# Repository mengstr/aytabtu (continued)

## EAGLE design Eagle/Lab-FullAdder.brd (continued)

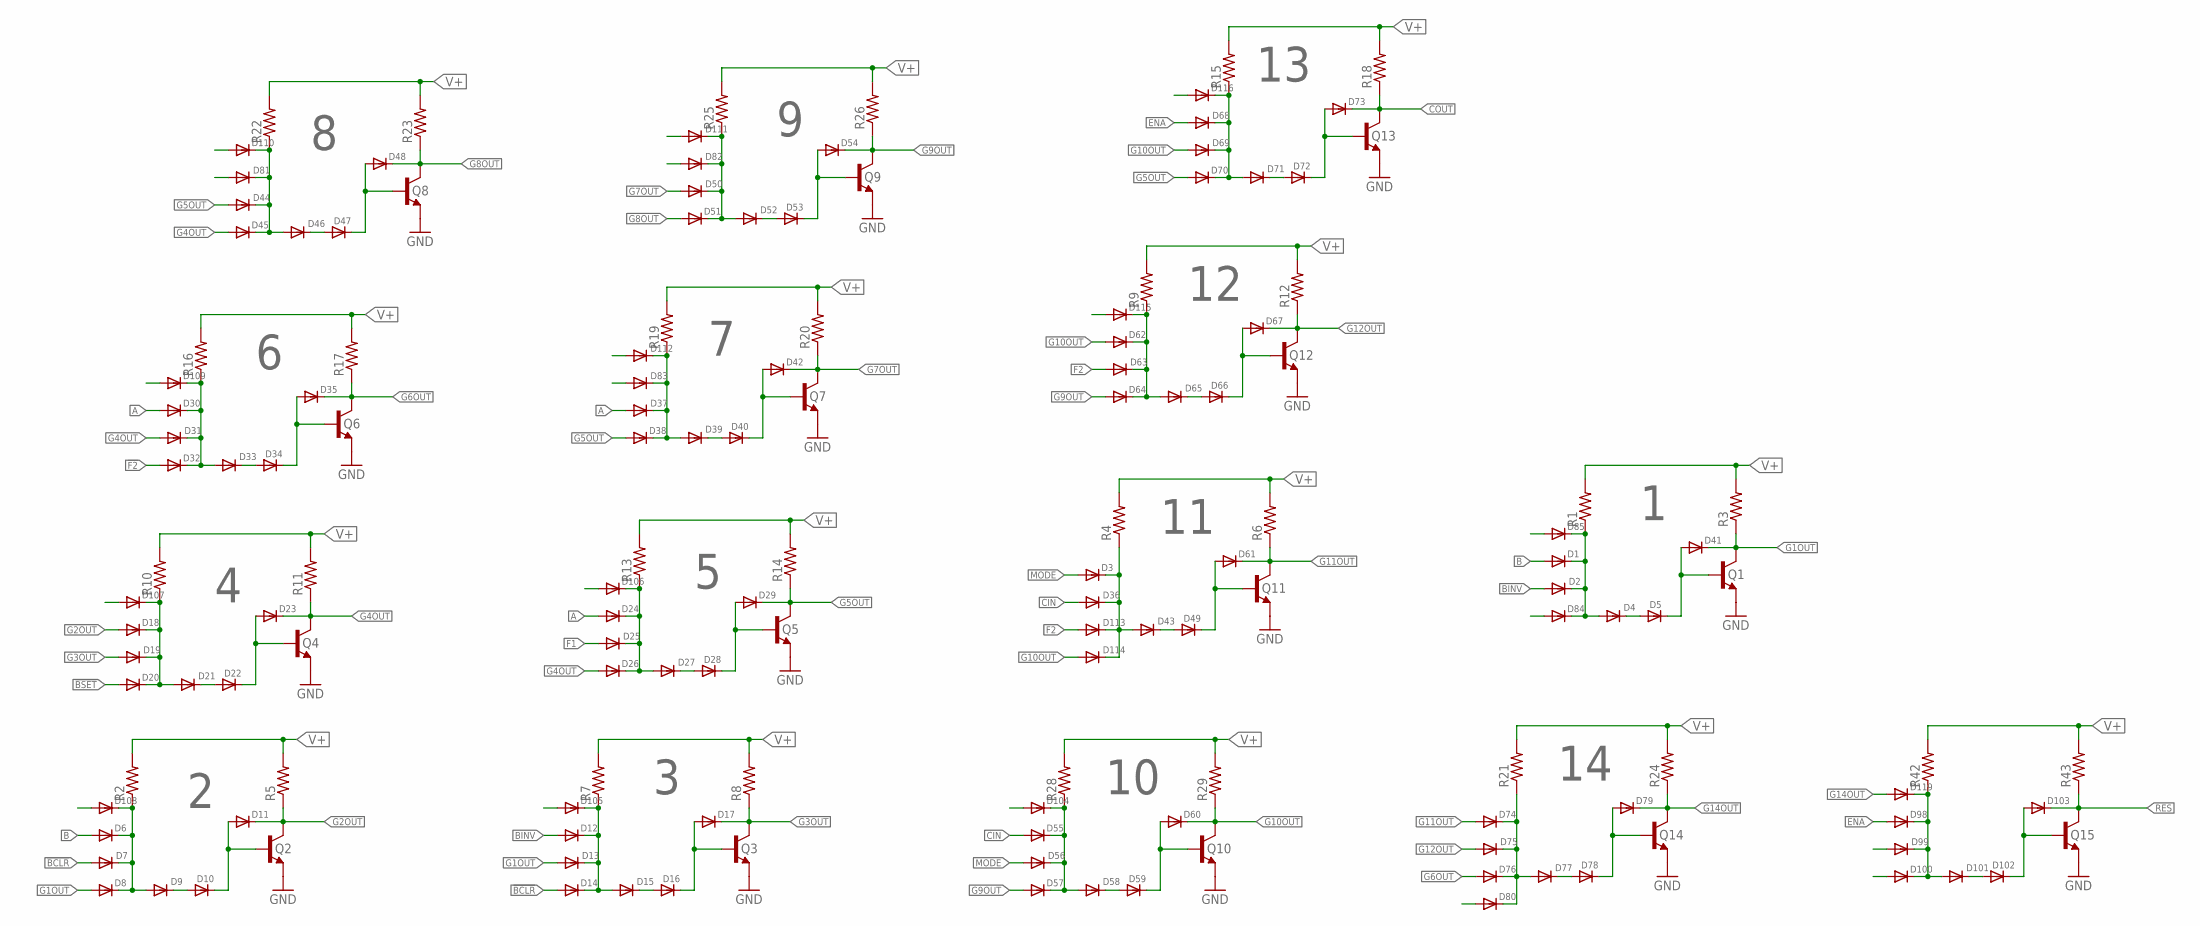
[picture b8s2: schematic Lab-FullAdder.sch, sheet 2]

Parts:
D1, D2, D3, D4, D5, D6, D7, D8, D9, D10, D12, D13, D14, D15, D16, D18, D19, D20, D21, D22, D24, D25, D26, D27, D28, D30, D31, D32, D33, D34, D36, D37, D38, D39, D40, D43, D44, D45, D46, D47, D49, D50, D51, D52, D53, D55, D56, D57, D58, D59, D62, D63, D64, D65, D66, D68, D69, D70, D71, D72, D74, D75, D76, D77, D78, D80, D81, D82, D83, D84, D85, D98, D99, D100, D101, D102, D104, D105, D106, D107, D108, D109, D110, D111, D112, D113, D114, D115, D116, D119: DIODE-6.3; DO35-6.3
D11, D17, D23, D29, D35, D41, D42, D48, D54, D60, D61, D67, D73, D79, D103: DIODE-7.6; DO35-7.6
Q1, Q2, Q3, Q4, Q5, Q6, Q7, Q8, Q9, Q10, Q11, Q12, Q13, Q14, Q15: 2N3904-1; TO92BH
R1, R2, R3, R4, R5, R6, R7, R8, R9, R10, R11, R12, R13, R14, R15, R16, R17, R18, R19, R20, R21, R22, R23, R24, R25, R26, R28, R29, R42, R43: R1/8-7.6MM; R0125-7.6

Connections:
!BCLR: D7.A, D14.A; also elsewhere on the board
!BSET: D20.A; also elsewhere on the board
!F2: D32.A; also elsewhere on the board
A: D24.A, D30.A, D37.A; also elsewhere on the board
B: D1.A, D6.A; also elsewhere on the board
BINV: D2.A, D12.A; also elsewhere on the board
CIN: D36.A, D55.A; also elsewhere on the board
COUT: D73.C, Q13.3 (C), R18.1; also elsewhere on the board
ENA: D68.A, D98.A; also elsewhere on the board
F1: D25.A; also elsewhere on the board
F2: D63.A, D113.A; also elsewhere on the board
G1OUT: D8.A, D13.A, D41.C, Q1.3 (C), R3.1
G2OUT: D11.C, D18.A, Q2.3 (C), R5.1
G3OUT: D17.C, D19.A, Q3.3 (C), R8.1
G4OUT: D23.C, D26.A, D31.A, D45.A, Q4.3 (C), R11.1
G5OUT: D29.C, D38.A, D44.A, D70.A, Q5.3 (C), R14.1
G6OUT: D35.C, D76.A, Q6.3 (C), R17.1
G7OUT: D42.C, D50.A, Q7.3 (C), R20.1
G8OUT: D48.C, D51.A, Q8.3 (C), R23.1
G9OUT: D54.C, D57.A, D64.A, Q9.3 (C), R26.1
G10OUT: D60.C, D62.A, D69.A, D114.A, Q10.3 (C), R29.1
G11OUT: D61.C, D74.A, Q11.3 (C), R6.1
G12OUT: D67.C, D75.A, Q12.3 (C), R12.1
G14OUT: D79.C, D119.A, Q14.3 (C), R24.1
GND: Q1.1 (E), Q2.1 (E), Q3.1 (E), Q4.1 (E), Q5.1 (E), Q6.1 (E), Q7.1 (E), Q8.1 (E), Q9.1 (E), Q10.1 (E), Q11.1 (E), Q12.1 (E), Q13.1 (E), Q14.1 (E), Q15.1 (E); also elsewhere on the board
MODE: D3.A, D56.A; also elsewhere on the board
unnamed: D1.C, D2.C, D4.A, D84.C, D85.C, R1.1
unnamed: D4.C, D5.A
unnamed: D5.C, D41.A, Q1.2 (B)
unnamed: D6.C, D7.C, D8.C, D9.A, D108.C, R2.1
unnamed: D9.C, D10.A
unnamed: D10.C, D11.A, Q2.2 (B)
unnamed: D3.C, D36.C, D43.A, D113.C, D114.C, R4.1
unnamed: D12.C, D13.C, D14.C, D15.A, D105.C, R7.1
unnamed: D15.C, D16.A
unnamed: D16.C, D17.A, Q3.2 (B)
unnamed: D43.C, D49.A
unnamed: D18.C, D19.C, D20.C, D21.A, D107.C, R10.1
unnamed: D21.C, D22.A
unnamed: D22.C, D23.A, Q4.2 (B)
unnamed: D49.C, D61.A, Q11.2 (B)
unnamed: D24.C, D25.C, D26.C, D27.A, D106.C, R13.1
unnamed: D27.C, D28.A
unnamed: D28.C, D29.A, Q5.2 (B)
unnamed: D30.C, D31.C, D32.C, D33.A, D109.C, R16.1
unnamed: D33.C, D34.A
unnamed: D34.C, D35.A, Q6.2 (B)
unnamed: D98.C, D99.C, D100.C, D101.A, D119.C, R42.1
unnamed: D37.C, D38.C, D39.A, D83.C, D112.C, R19.1
unnamed: D39.C, D40.A
unnamed: D40.C, D42.A, Q7.2 (B)
unnamed: D101.C, D102.A
unnamed: D102.C, D103.A, Q15.2 (B)
unnamed: D62.C, D63.C, D64.C, D65.A, D115.C, R9.1
unnamed: D44.C, D45.C, D46.A, D81.C, D110.C, R22.1
unnamed: D46.C, D47.A
unnamed: D47.C, D48.A, Q8.2 (B)
unnamed: D65.C, D66.A
unnamed: D66.C, D67.A, Q12.2 (B)
unnamed: D50.C, D51.C, D52.A, D82.C, D111.C, R25.1
unnamed: D52.C, D53.A
unnamed: D53.C, D54.A, Q9.2 (B)
unnamed: D55.C, D56.C, D57.C, D58.A, D104.C, R28.1
unnamed: D58.C, D59.A
unnamed: D59.C, D60.A, Q10.2 (B)
unnamed: D68.C, D69.C, D70.C, D71.A, D116.C, R15.1
unnamed: D71.C, D72.A
unnamed: D72.C, D73.A, Q13.2 (B)
unnamed: D74.C, D75.C, D76.C, D77.A, D80.C, R21.1
unnamed: D77.C, D78.A
unnamed: D78.C, D79.A, Q14.2 (B)
RES: D103.C, Q15.3 (C), R43.1; also elsewhere on the board
V+: R1.2, R2.2, R3.2, R4.2, R5.2, R6.2, R7.2, R8.2, R9.2, R10.2, R11.2, R12.2, R13.2, R14.2, R15.2, R16.2, R17.2, R18.2, R19.2, R20.2, R21.2, R22.2, R23.2, R24.2, R25.2, R26.2, R28.2, R29.2, R42.2, R43.2; also elsewhere on the board

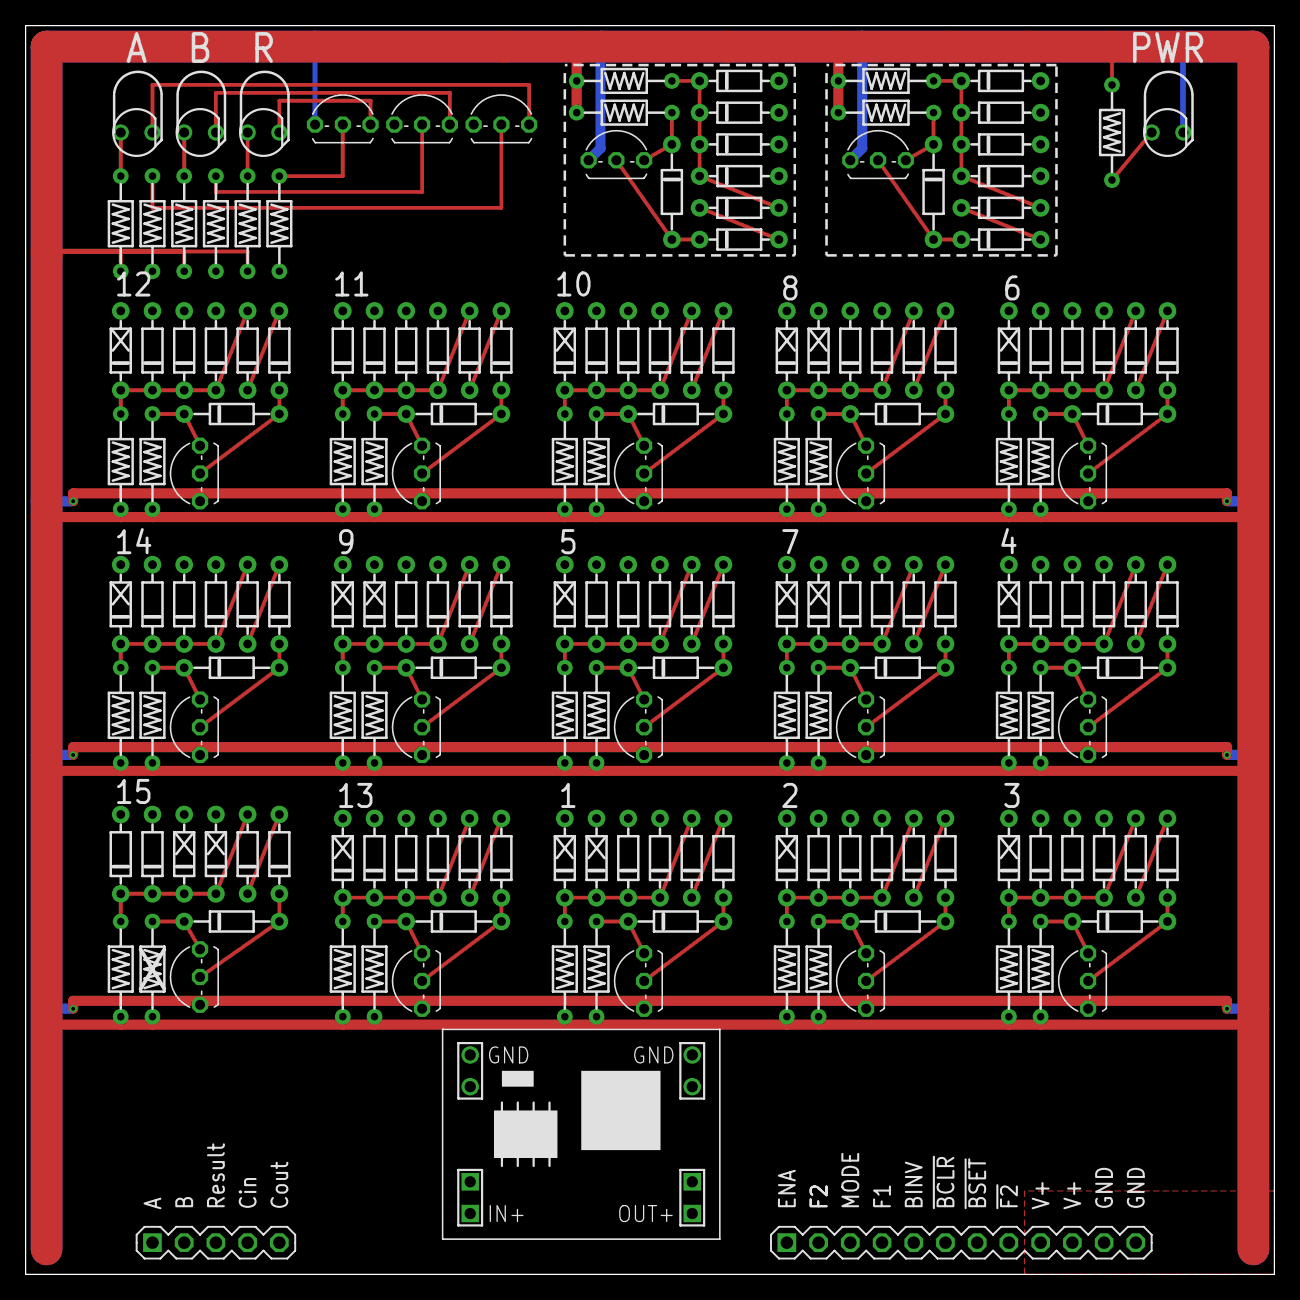
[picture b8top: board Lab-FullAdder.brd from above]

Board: 2 copper layers, 100.0 x 100.0 mm, 187 parts (0 on the bottom side), 93 nets.

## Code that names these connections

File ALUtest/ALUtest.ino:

#define MODE   2
#define CI     3
#define F2     4
#define A      5
#define F1     6
#define B      7
#define BINV   8
#define BCLR_  9
#define BSET_ 10
#define F2_   11
#define ENA   12
#define RESULT A0
#define COUT   A1


void setup() {
  Serial.begin(9600); 
  while (!Serial) {
    ; // wait for serial port to connect. Needed for Leonardo only
  }
  Serial.println("AYTABTU ALU Slice tester");
  
  pinMode(MODE,OUTPUT);
  pinMode(CI,OUTPUT);
  pinMode(F2,OUTPUT);
  pinMode(A,OUTPUT);
  pinMode(F1,OUTPUT);
  pinMode(B,OUTPUT);
  pinMode(BINV,OUTPUT);
  pinMode(BCLR_,OUTPUT);
  pinMode(BSET_,OUTPUT);
  pinMode(F2_,OUTPUT);
  pinMode(ENA,OUTPUT);
  pinMode(RESULT, INPUT);
  pinMode(COUT, INPUT);

  TestXor();
  TestOr();
  TestAnd();
  TestZero();
  TestOne();
  TestNot();
  TestInc();
  TestDec();
}


char *Scan(void) {
  static char table[1000];
  table[0]=0;

  strcat(table,"AB Ci- R Co\n");
  strcat(table,"===========\n");

  digitalWrite(A,LOW); digitalWrite(B,LOW); digitalWrite(CI,LOW);
  strcat(table,"00 0 - ");
  if (digitalRead(RESULT)==HIGH) strcat(table,"1 "); else strcat(table,"0 "); 
  if (digitalRead(COUT)==HIGH) strcat(table,"1\n"); else strcat(table,"0\n"); 
  
  digitalWrite(A,HIGH); digitalWrite(B,LOW); digitalWrite(CI,LOW);
  strcat(table,"10 0 - ");
  if (digitalRead(RESULT)==HIGH) strcat(table,"1 "); else strcat(table,"0 "); 
  if (digitalRead(COUT)==HIGH) strcat(table,"1\n"); else strcat(table,"0\n"); 

  digitalWrite(A,LOW); digitalWrite(B,HIGH); digitalWrite(CI,LOW);
  strcat(table,"01 0 - ");
  if (digitalRead(RESULT)==HIGH) strcat(table,"1 "); else strcat(table,"0 "); 
  if (digitalRead(COUT)==HIGH) strcat(table,"1\n"); else strcat(table,"0\n"); 

  digitalWrite(A,HIGH); digitalWrite(B,HIGH); digitalWrite(CI,LOW);
  strcat(table,"11 0 - ");
  if (digitalRead(RESULT)==HIGH) strcat(table,"1 "); else strcat(table,"0 "); 
  if (digitalRead(COUT)==HIGH) strcat(table,"1\n"); else strcat(table,"0\n"); 

  digitalWrite(A,LOW); digitalWrite(B,LOW); digitalWrite(CI,HIGH);
  strcat(table,"00 1 - ");
  if (digitalRead(RESULT)==HIGH) strcat(table,"1 "); else strcat(table,"0 "); 
  if (digitalRead(COUT)==HIGH) strcat(table,"1\n"); else strcat(table,"0\n"); 
  
  digitalWrite(A,HIGH); digitalWrite(B,LOW); digitalWrite(CI,HIGH);
  strcat(table,"10 1 - ");
  if (digitalRead(RESULT)==HIGH) strcat(table,"1 "); else strcat(table,"0 "); 
  if (digitalRead(COUT)==HIGH) strcat(table,"1\n"); else strcat(table,"0\n"); 

  digitalWrite(A,LOW); digitalWrite(B,HIGH); digitalWrite(CI,HIGH);
  strcat(table,"01 1 - ");
  if (digitalRead(RESULT)==HIGH) strcat(table,"1 "); else strcat(table,"0 "); 
  if (digitalRead(COUT)==HIGH) strcat(table,"1\n"); else strcat(table,"0\n"); 

  digitalWrite(A,HIGH); digitalWrite(B,HIGH); digitalWrite(CI,HIGH);
  strcat(table,"11 1 - ");
  if (digitalRead(RESULT)==HIGH) strcat(table,"1 "); else strcat(table,"0 "); 
  if (digitalRead(COUT)==HIGH) strcat(table,"1\n"); else strcat(table,"0\n"); 

  return table;
}


void TestXor(void) {
  char *pLine;
  digitalWrite(ENA,   HIGH);
  digitalWrite(MODE,  LOW);
  digitalWrite(F1,    HIGH);
  digitalWrite(F2,    HIGH);
  digitalWrite(F2_,   LOW);
  digitalWrite(BCLR_, HIGH);
  digitalWrite(BSET_, HIGH);
  digitalWrite(BINV,  LOW);
  pLine=Scan();
  Serial.println("\n*** XOR ***\n");
  Serial.println(pLine); 
}


void TestOr(void) {
  char *pLine;
  digitalWrite(ENA,   HIGH);
  digitalWrite(MODE,  LOW);
  digitalWrite(F1,    LOW);
  digitalWrite(F2,    HIGH);
  digitalWrite(F2_,   LOW);
  digitalWrite(BCLR_, HIGH);
  digitalWrite(BSET_, HIGH);
  digitalWrite(BINV,  LOW);
  pLine=Scan();
  Serial.println("\n*** OR ***\n");
  Serial.println(pLine); 
}

void TestAnd(void) {
  char *pLine;
  digitalWrite(ENA,   HIGH);
  digitalWrite(MODE,  LOW);
  digitalWrite(F1,    LOW);
  digitalWrite(F2,    LOW);
  digitalWrite(F2_,   HIGH);
  digitalWrite(BCLR_, HIGH);
  digitalWrite(BSET_, HIGH);
  digitalWrite(BINV,  LOW);
  pLine=Scan();
  Serial.println("\n*** AND ***\n");
  Serial.println(pLine); 
}


void TestZero(void) {
  char *pLine;
  digitalWrite(ENA,   HIGH);
  digitalWrite(MODE,  LOW);
  digitalWrite(F1,    LOW);
  digitalWrite(F2,    LOW);
  digitalWrite(F2_,   HIGH);
  digitalWrite(BCLR_, LOW);
  digitalWrite(BSET_, HIGH);
  digitalWrite(BINV,  LOW);
  pLine=Scan();
  Serial.println("\n*** ZERO ***\n");
  Serial.println(pLine); 
}

void TestOne(void) {
  char *pLine;
  digitalWrite(ENA,   HIGH);
  digitalWrite(MODE,  LOW);
  digitalWrite(F1,    LOW);
  digitalWrite(F2,    LOW);
  digitalWrite(F2_,   HIGH);
  digitalWrite(BCLR_, HIGH);
  digitalWrite(BSET_, LOW);
  digitalWrite(BINV,  LOW);
  pLine=Scan();
  Serial.println("\n*** ONE ***\n");
  Serial.println(pLine); 
}

void TestNot(void) {
  char *pLine;
  digitalWrite(ENA,   HIGH);
  digitalWrite(MODE,  LOW);
  digitalWrite(F1,    HIGH);
  digitalWrite(F2,    HIGH);
  digitalWrite(F2_,   LOW);
  digitalWrite(BCLR_, HIGH);
  digitalWrite(BSET_, LOW);
  digitalWrite(BINV,  LOW);
  pLine=Scan();
  Serial.println("\n*** ZERO ***\n");
  Serial.println(pLine); 
}


void TestInc(void) {
  char *pLine;
  digitalWrite(ENA,   HIGH);
  digitalWrite(MODE,  HIGH);
  digitalWrite(F1,    HIGH);
  digitalWrite(F2,    HIGH);
  digitalWrite(F2_,   LOW);
  digitalWrite(BCLR_, LOW);
  digitalWrite(BSET_, HIGH);
  digitalWrite(BINV,  HIGH);
  pLine=Scan();
  Serial.println("\n*** INC ***\n");
  Serial.println(pLine); 
}

void TestDec(void) {
  char *pLine;
  digitalWrite(ENA,   HIGH);
  digitalWrite(MODE,  HIGH);
  digitalWrite(F1,    HIGH);
  digitalWrite(F2,    HIGH);
  digitalWrite(F2_,   LOW);
  digitalWrite(BCLR_, HIGH);
  digitalWrite(BSET_, LOW);
  digitalWrite(BINV,  LOW);
  pLine=Scan();
  Serial.println("\n*** DEC ***\n");
  Serial.println(pLine); 
}


void loop() {
}

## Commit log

2015-07-07 Files for UART RX
2015-07-13 Added LTspice files to .gitignore
2015-07-13 Fixed comparator
2015-07-13 Ramp is now falling
2015-07-13 Removed neg voltage and one level shifter diode
2015-07-13 Changed to new Comparator
2015-07-13 Added delayed faker and gitch faker
2015-07-13 Added glitc detection
2015-07-13 Added comment/heading in schematics
2015-07-13 Added voltage-in for TX fakers
2015-07-13 Added cap to get filtering of spurs from data-line
2015-07-13 Went back to rising ramp, reversed polarity on divider ladder
2015-07-13 Added ACK signal from CPU
2015-07-13 Removed testharness from UART-RX to own modolu
2015-07-13 Added octal addressable latch to UART-RX
2015-07-13 Ignore LTspice Draft*.asc files
2015-07-14 Stonger pulldown at output PNP
2015-07-15 Added 12-step ringcounter for UART-TX
2015-07-15 Unknown updates :-(
2015-07-15 Added layouts for donut-pcbs
2015-07-15 Update README with some links
2015-07-15 Added calculator for resistor divider
2015-07-15 Eagle files
2015-07-15 Added .pro -files to .gitignore
2015-07-15 Added some images
2015-07-16 Some more pictures
2015-07-16 Added internal routing of modules
2015-07-16 Named the NAND gates to match internal routing image
2015-07-16 Updated README with more links
2015-07-17 More images
2015-07-17 More links in README
2015-07-17 Half done assembler for cpu
2015-07-17 Documentation of instructionset
2015-07-20 Added Program Memory instructions to instruction set
2015-07-20 Centralized error handling.
2015-07-20 Now two-pass assembler that can resolve forward references
2015-07-24 Update of error im base values in opcodes
2015-07-24 First version of cpu emulator
2015-07-24 Added tcp server for emulating uart on in/out[15]
2015-07-27 Updates and short test code to emulate
2015-07-27 Frontpanel design
2015-07-27 Uart rx/tx working
2015-08-27 General flush of files
